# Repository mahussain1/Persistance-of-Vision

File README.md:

# Persistance of Vision
Persistence of Vision or POV is based on human vision capability. It works using the fact that human eye is unable to detect change within 1/16 sec. LEDs were mounted on flat strip of PCB attached with stepper motor. Further on basis of coding, different effects could be observed while rotating.

## Delay Calculation
It is important to set delay of Leds on and off time to clearly visulize the characters while rotating. So for calculating delay, following strategy was used as shown in figure.

*Formula to calculate delay*

## Character Combination for 5 and 12 Leds Strip

To generate different charater combination, Every led is considered as binary digit. Suppose to display one digit as straight verticle line on 5 leds, we have to turn on all leds at same time. So the arrary values will be like: 1+2+4+8+16 = 31. So 31 will be stored in array to display a straight line. This technique is followed for each character to create an array. See Example figure below to have some graphical overview.

*Technique to calculate an array combination*

## PCB Schematic and Board file Snapshots
The Schematic and PCB file was designed using Eagle CAD Software. 

## Componenets
* Atmel's Atmega 168-20P
* Stepper Motor
* Lipo Battery
* Electronic Speed Control (ESC)
* HC-05 Bluetooth Sensor
* Transistors, Voltage Regulator
* RGB Leds, Resistors, Capacitors

### Acknowledgement
This project was completed during my internship at [FAB LAB Sukkur IBA University](http://fablab.iba-suk.edu.pk/) in 2017. I am thankful to Engr. Dr. Muhammad Asim Ali Samejo and Fab Lab instructor Engr. Manzar Hussain Laghari for their guidance.

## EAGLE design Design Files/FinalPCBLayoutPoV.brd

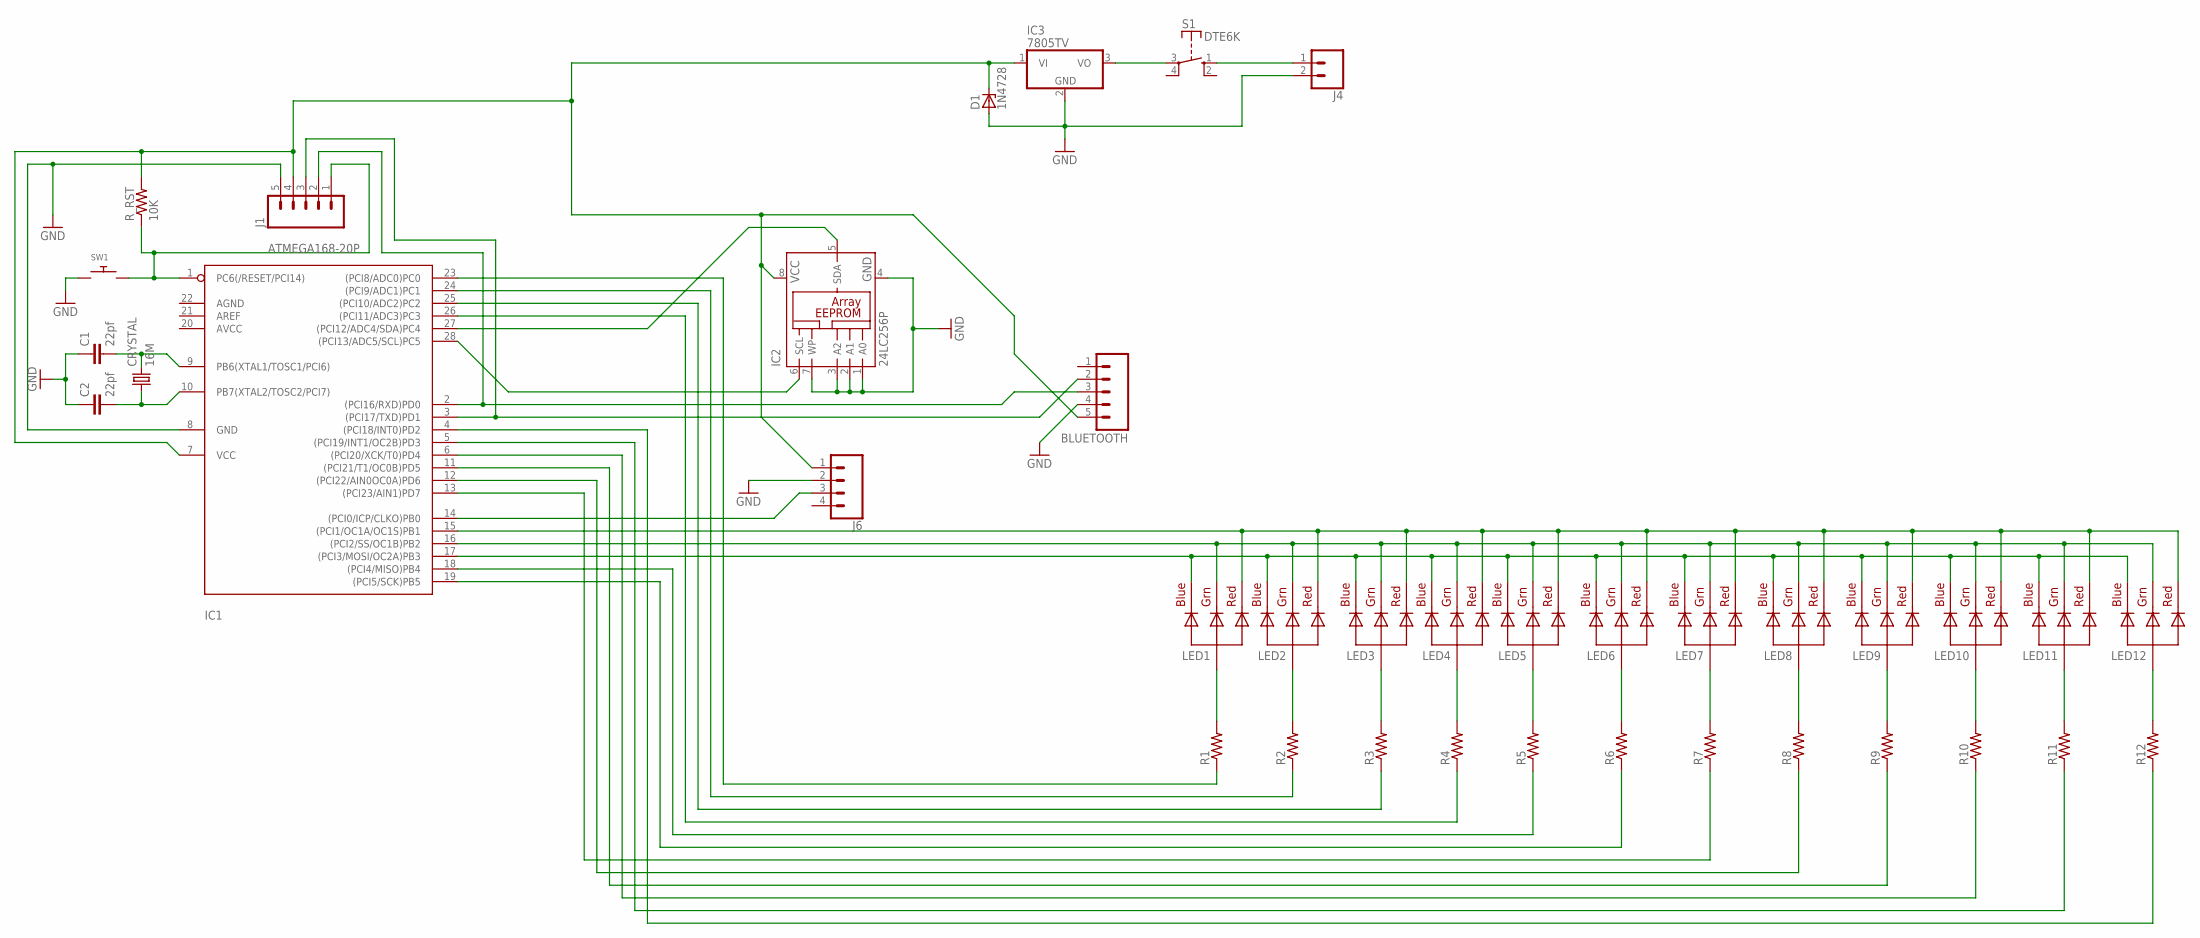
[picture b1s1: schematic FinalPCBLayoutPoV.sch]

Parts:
BLUETOOTH: M05SCREW; SCREWTERMINAL-3.5MM-5
C1, C2: 22pf; C025-060X050
CRYSTAL: 16M; HC49/S
D1: 1N4728; DO41Z10
IC1: ATMEGA168-20P; DIL28-3
IC2: 24LC256P; DIL8
IC3: 7805TV; TO220V
J1: M05SCREW; SCREWTERMINAL-3.5MM-5
J4: CONN_02PTH3; 1X02_LONGPADS
J6: CONN_04LONGPADS; 1X04_LONGPADS
LED1, LED2, LED3, LED4, LED5, LED6, LED7, LED8, LED9, LED10, LED11, LED12: RGBLED_CA-5MM; LED5MMRGB
R1, R2, R3, R4, R5, R6, R7, R8, R9, R10, R11, R12: R-US_0207/10; 0207/10
R_RST: 10K; 0207/10
S1: DTE6K
SW1: SWITCH_PUSHBUTTONEVQ-PE; TACT_PANA-EVQ

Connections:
CRTL1: C1.2, CRYSTAL.2, IC1.9 (PB6(XTAL1/TOSC1/PCI6))
CRTL2: C2.2, CRYSTAL.1, IC1.10 (PB7(XTAL2/TOSC2/PCI7))
CRX-BTX: BLUETOOTH.3, IC1.2 ((PCI16/RXD)PD0), J1.2
CTX-BRX: BLUETOOTH.2, IC1.3 ((PCI17/TXD)PD1), J1.3
GND: BLUETOOTH.4, C1.1, C2.1, D1.A, IC1.8 (GND), IC2.1 (A0), IC2.2 (A1), IC2.3 (A2), IC2.4 (GND), IC2.7 (WP), IC3.2 (GND), J1.5, J4.2, J6.2, SW1.P$1
LED1: IC1.23 ((PCI8/ADC0)PC0), R1.1
LED2: IC1.24 ((PCI9/ADC1)PC1), R2.1
LED3: IC1.25 ((PCI10/ADC2)PC2), R3.1
LED4: IC1.26 ((PCI11/ADC3)PC3), R4.1
LED5: IC1.18 ((PCI4/MISO)PB4), R5.1
LED6: IC1.19 ((PCI5/SCK)PB5), R6.1
LED7: IC1.13 ((PCI23/AIN1)PD7), R7.1
LED8: IC1.12 ((PCI22/AIN0OC0A)PD6), R8.1
LED9: IC1.11 ((PCI21/T1/OC0B)PD5), R9.1
LED10: IC1.6 ((PCI20/XCK/T0)PD4), R10.1
LED11: IC1.5 ((PCI19/INT1/OC2B)PD3), R11.1
LED12: IC1.4 ((PCI18/INT0)PD2), R12.1
unnamed: IC3.3 (VO), S1.3
unnamed: J4.1, S1.1 (S)
unnamed: IC1.14 ((PCI0/ICP/CLKO)PB0), J6.3
unnamed: IC1.27 ((PCI12/ADC4/SDA)PC4), IC2.5 (SDA)
unnamed: IC1.28 ((PCI13/ADC5/SCL)PC5), IC2.6 (SCL)
unnamed: LED1.2 (VCC), R1.2
unnamed: LED2.2 (VCC), R2.2
unnamed: LED3.2 (VCC), R3.2
unnamed: LED4.2 (VCC), R4.2
unnamed: LED5.2 (VCC), R5.2
unnamed: LED6.2 (VCC), R6.2
unnamed: LED7.2 (VCC), R7.2
unnamed: LED8.2 (VCC), R8.2
unnamed: LED9.2 (VCC), R9.2
unnamed: LED10.2 (VCC), R10.2
unnamed: LED11.2 (VCC), R11.2
unnamed: LED12.2 (VCC), R12.2
PWM-BLUE: IC1.17 ((PCI3/MOSI/OC2A)PB3), LED1.4 (BLUE), LED2.4 (BLUE), LED3.4 (BLUE), LED4.4 (BLUE), LED5.4 (BLUE), LED6.4 (BLUE), LED7.4 (BLUE), LED8.4 (BLUE), LED9.4 (BLUE), LED10.4 (BLUE), LED11.4 (BLUE), LED12.4 (BLUE)
PWM-GREEN: IC1.16 ((PCI2/SS/OC1B)PB2), LED1.3 (GREEN), LED2.3 (GREEN), LED3.3 (GREEN), LED4.3 (GREEN), LED5.3 (GREEN), LED6.3 (GREEN), LED7.3 (GREEN), LED8.3 (GREEN), LED9.3 (GREEN), LED10.3 (GREEN), LED11.3 (GREEN), LED12.3 (GREEN)
PWM-READ: IC1.15 ((PCI1/OC1A/OC1S)PB1), LED1.1 (RED), LED2.1 (RED), LED3.1 (RED), LED4.1 (RED), LED5.1 (RED), LED6.1 (RED), LED7.1 (RED), LED8.1 (RED), LED9.1 (RED), LED10.1 (RED), LED11.1 (RED), LED12.1 (RED)
RST: IC1.1 (PC6(/RESET/PCI14)), J1.1, R_RST.1, SW1.P$2
VCC1: BLUETOOTH.5, D1.C, IC1.7 (VCC), IC2.8 (VCC), IC3.1 (VI), J1.4, J6.1, R_RST.2

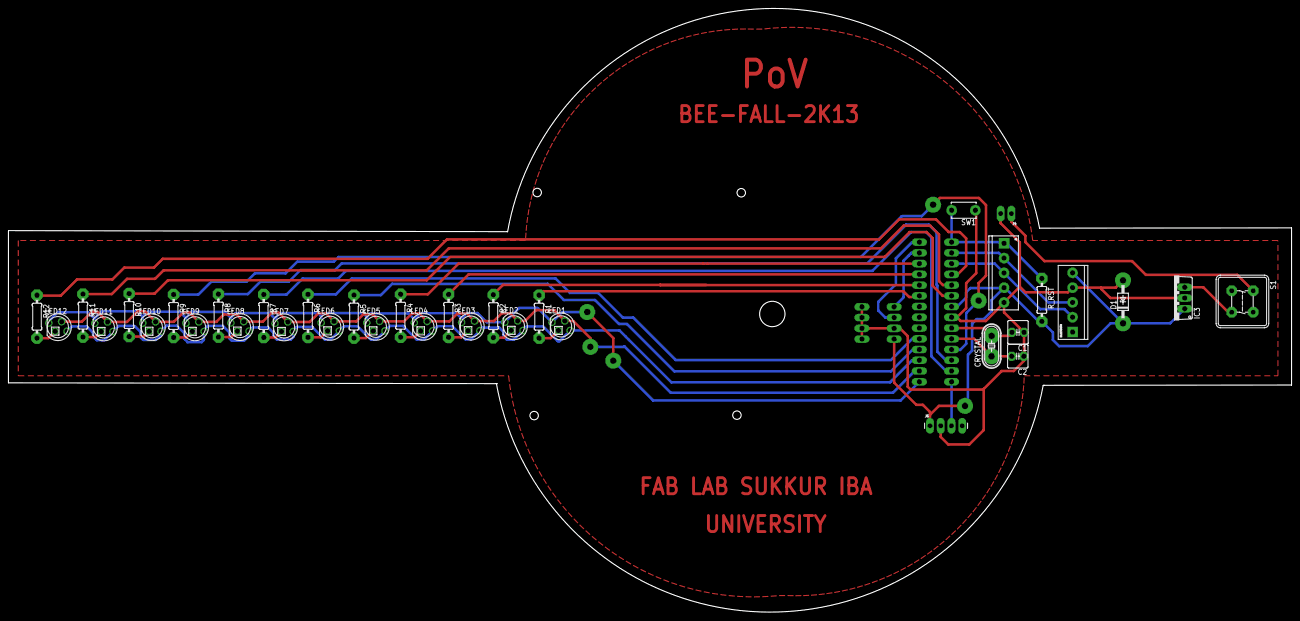
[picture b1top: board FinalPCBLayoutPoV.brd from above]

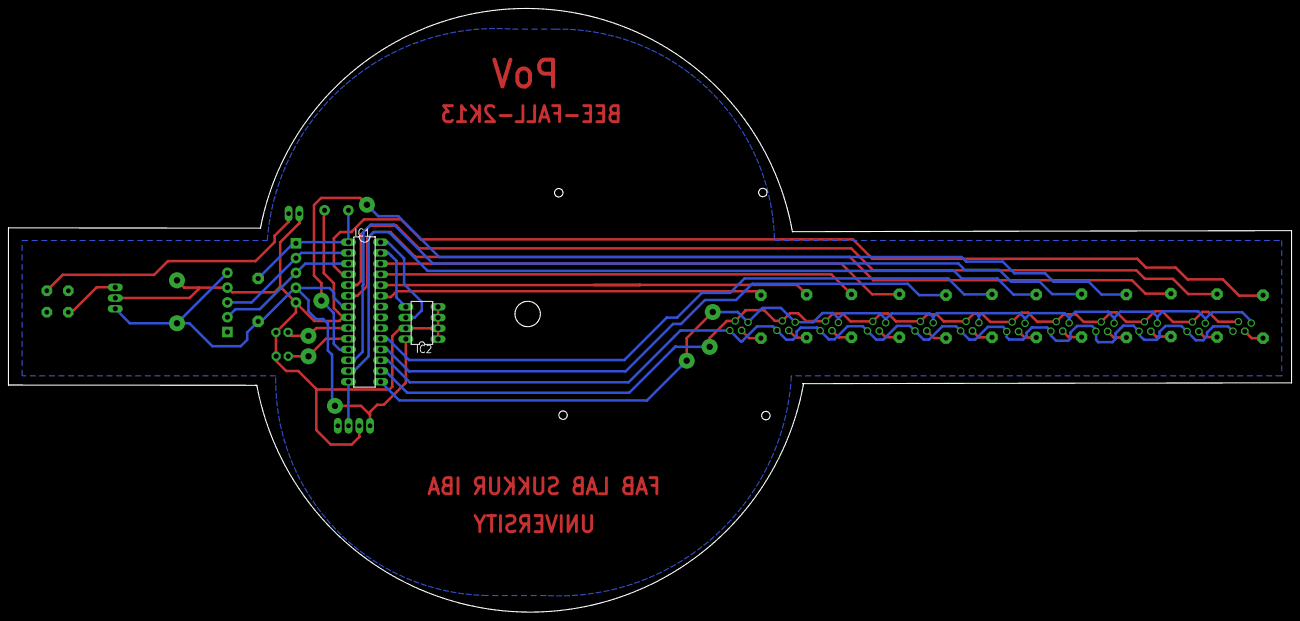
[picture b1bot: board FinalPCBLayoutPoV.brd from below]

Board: 2 copper layers, 303.6 x 142.8 mm, 38 parts (2 on the bottom side), 39 nets.

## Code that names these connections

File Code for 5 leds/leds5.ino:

   int red[]=  {255,255,255,0  ,0  ,138, 0 , 0 ,127,255,255,127,138,127,255,255};
   int green[]={ 0 ,128,255,255,255, 48,255, 0 ,0  ,0  ,0  ,255,43 ,255,255,140};
   int blue[]= { 0 ,0  , 0 , 0 ,255,226, 0 ,255,255,255,127,212,226, 0 ,255, 0 };
   
int delayTime = 1000;
int charBreak = 2.1;
int LED1 = 2;
int LED2 = 3;
int LED3 = 4;
int LED4 = 5;
int LED5 = 6;

   int rr=9; 
   int gg=10;
   int bb=11;
   
   String value="siba";
   String val;
   char textString[]="";
   

void setup(){
pinMode(LED1, OUTPUT);
pinMode(LED2, OUTPUT);
pinMode(LED3, OUTPUT);
pinMode(LED4, OUTPUT);
pinMode(LED5, OUTPUT);

pinMode(rr, OUTPUT);
pinMode(gg, OUTPUT);
pinMode(bb, OUTPUT);

 analogWrite(rr,126); 
 analogWrite(gg,222); 
 analogWrite(bb,100);
}

void colorSelect(int colorIndex){
 analogWrite(rr,red[colorIndex]); 
 analogWrite(gg,green[colorIndex]); 
 analogWrite(bb,blue[colorIndex]); 

}

int a[] = {1, 6, 26, 6, 1};
int b[] = {31, 21, 21, 10, 0};
int c2[] = {14, 17, 17, 10, 0};
int d[] = {31, 17, 17, 14, 0};
int e[] = {31, 21, 21, 17, 0};
int f[] = {31, 20, 20, 16, 0};
int g[] = {14, 17, 19, 10, 0};
int h[] = {31, 4, 4, 4, 31};
int i[] = {0, 17, 31, 17, 0};
int j[] = {0, 17, 30, 16, 0};
int k[] = {31, 4, 10, 17, 0};
int l[] = {31, 1, 1, 1, 0};
int m[] = {31, 12, 3, 12, 31};
int n[] = {31, 12, 3, 31, 0};
int o[] = {14, 17, 17, 14, 0};
int p[] = {31, 20, 20, 8, 0};
int q[] = {14, 17, 19, 14, 2};
int r[] = {31, 20, 22, 9, 0};
int s[] = {8, 21, 21, 2, 0};
int t[] = {16, 16, 31, 16, 16};
int u[] = {30, 1, 1, 30, 0};
int v[] = {24, 6, 1, 6, 24};
int w[] = {28, 3, 12, 3, 28};
int x[] = {17, 10, 4, 10, 17};
int y[] = {17, 10, 4, 8, 16};
int z[] = {19, 21, 21, 25, 0};

int eos[] = {0, 1, 0, 0, 0};
int excl[] = {0, 29, 0, 0, 0};
int ques[] = {8, 19, 20, 8, 0};

void displayLine(int line){
int myline;
myline = line;
colorSelect(random(15));
if (myline>=16) {digitalWrite(LED1, LOW); myline-=16;} else {digitalWrite(LED1, HIGH);}
if (myline>=8)  {digitalWrite(LED2, LOW); myline-=8;}  else {digitalWrite(LED2,HIGH);}
if (myline>=4)  {digitalWrite(LED3, LOW); myline-=4;}  else {digitalWrite(LED3, HIGH);}
if (myline>=2)  {digitalWrite(LED4, LOW); myline-=2;}  else {digitalWrite(LED4, HIGH);}
if (myline>=1)  {digitalWrite(LED5, LOW); myline-=1;}  else {digitalWrite(LED5, HIGH);}
}

void displayChar(char c){
if (c == 'a'){for (int i = 0; i <5; i++){displayLine(a[i]);delay(delayTime);}displayLine(0);}
if (c == 'b'){for (int i = 0; i <5; i++){displayLine(b[i]);delay(delayTime);}displayLine(0);}
if (c == 'c'){for (int i = 0; i <5; i++){displayLine(c2[i]);delay(delayTime);}displayLine(0);}
if (c == 'd'){for (int i = 0; i <5; i++){displayLine(d[i]);delay(delayTime);}displayLine(0);}
if (c == 'e'){for (int i = 0; i <5; i++){displayLine(e[i]);delay(delayTime);}displayLine(0);}
if (c == 'f'){for (int i = 0; i <5; i++){displayLine(f[i]);delay(delayTime);}displayLine(0);}
if (c == 'g'){for (int i = 0; i <5; i++){displayLine(g[i]);delay(delayTime);}displayLine(0);}
if (c == 'h'){for (int i = 0; i <5; i++){displayLine(h[i]);delay(delayTime);}displayLine(0);}
if (c == 'i'){for (int it = 0; it <5; it++){displayLine(i[it]);delay(delayTime);}displayLine(0);}
if (c == 'j'){for (int i = 0; i <5; i++){displayLine(j[i]);delay(delayTime);}displayLine(0);}
if (c == 'k'){for (int i = 0; i <5; i++){displayLine(k[i]);delay(delayTime);}displayLine(0);}
if (c == 'l'){for (int i = 0; i <5; i++){displayLine(l[i]);delay(delayTime);}displayLine(0);}
if (c == 'm'){for (int i = 0; i <5; i++){displayLine(m[i]);delay(delayTime);}displayLine(0);}
if (c == 'n'){for (int i = 0; i <5; i++){displayLine(n[i]);delay(delayTime);}displayLine(0);}
if (c == 'o'){for (int i = 0; i <5; i++){displayLine(o[i]);delay(delayTime);}displayLine(0);}
if (c == 'p'){for (int i = 0; i <5; i++){displayLine(p[i]);delay(delayTime);}displayLine(0);}
if (c == 'q'){for (int i = 0; i <5; i++){displayLine(q[i]);delay(delayTime);}displayLine(0);}
if (c == 'r'){for (int i = 0; i <5; i++){displayLine(r[i]);delay(delayTime);}displayLine(0);}
if (c == 's'){for (int i = 0; i <5; i++){displayLine(s[i]);delay(delayTime);}displayLine(0);}
if (c == 't'){for (int i = 0; i <5; i++){displayLine(t[i]);delay(delayTime);}displayLine(0);}
if (c == 'u'){for (int i = 0; i <5; i++){displayLine(u[i]);delay(delayTime);}displayLine(0);}
if (c == 'v'){for (int i = 0; i <5; i++){displayLine(v[i]);delay(delayTime);}displayLine(0);}
if (c == 'w'){for (int i = 0; i <5; i++){displayLine(w[i]);delay(delayTime);}displayLine(0);}
if (c == 'x'){for (int i = 0; i <5; i++){displayLine(x[i]);delay(delayTime);}displayLine(0);}
if (c == 'y'){for (int i = 0; i <5; i++){displayLine(y[i]);delay(delayTime);}displayLine(0);}
if (c == 'z'){for (int i = 0; i <5; i++){displayLine(z[i]);delay(delayTime);}displayLine(0);}
if (c == '!'){for (int i = 0; i <5; i++){displayLine(excl[i]);delay(delayTime);}displayLine(0);}
if (c == '?'){for (int i = 0; i <5; i++){displayLine(ques[i]);delay(delayTime);}displayLine(0);}
if (c == '.'){for (int i = 0; i <5; i++){displayLine(eos[i]);delay(delayTime);}displayLine(0);}
delay(charBreak);
}

void displayString(char* s){
for (int i = 0; i<=strlen(s); i++){
displayChar(s[i]);
 
delay(2);
}
}

/*void colorSelect(){
 analogWrite(r,126); 
 analogWrite(g,222); 
 analogWrite(b,100); 
  }
*/
void loop(){

 if(Serial.available()>0){   //bluetooth data
        val= Serial.readStringUntil('\n');
        value=val;
        }
      else{
        value=value;
        }  
        
      textString[value.length()+1];
      value.toCharArray(textString,value.length()+1);      //string to char casting
      displayString(textString);
      delay(10); 
}

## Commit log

2019-12-05 Create gitkeep

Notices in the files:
parts and their libraries:
SparkFun-ConnectorsModified: Licensing: Creative Commons ShareAlike 4.0 International - https://creativecommons.org/licenses/by-sa/4.0
